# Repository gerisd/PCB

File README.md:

# PCB
PCB Hardware Design

# Overview

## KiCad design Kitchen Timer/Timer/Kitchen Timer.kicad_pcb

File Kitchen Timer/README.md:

# Kitchen Timer

## Results
### Schematic

### PCB 

### PCB 3D View

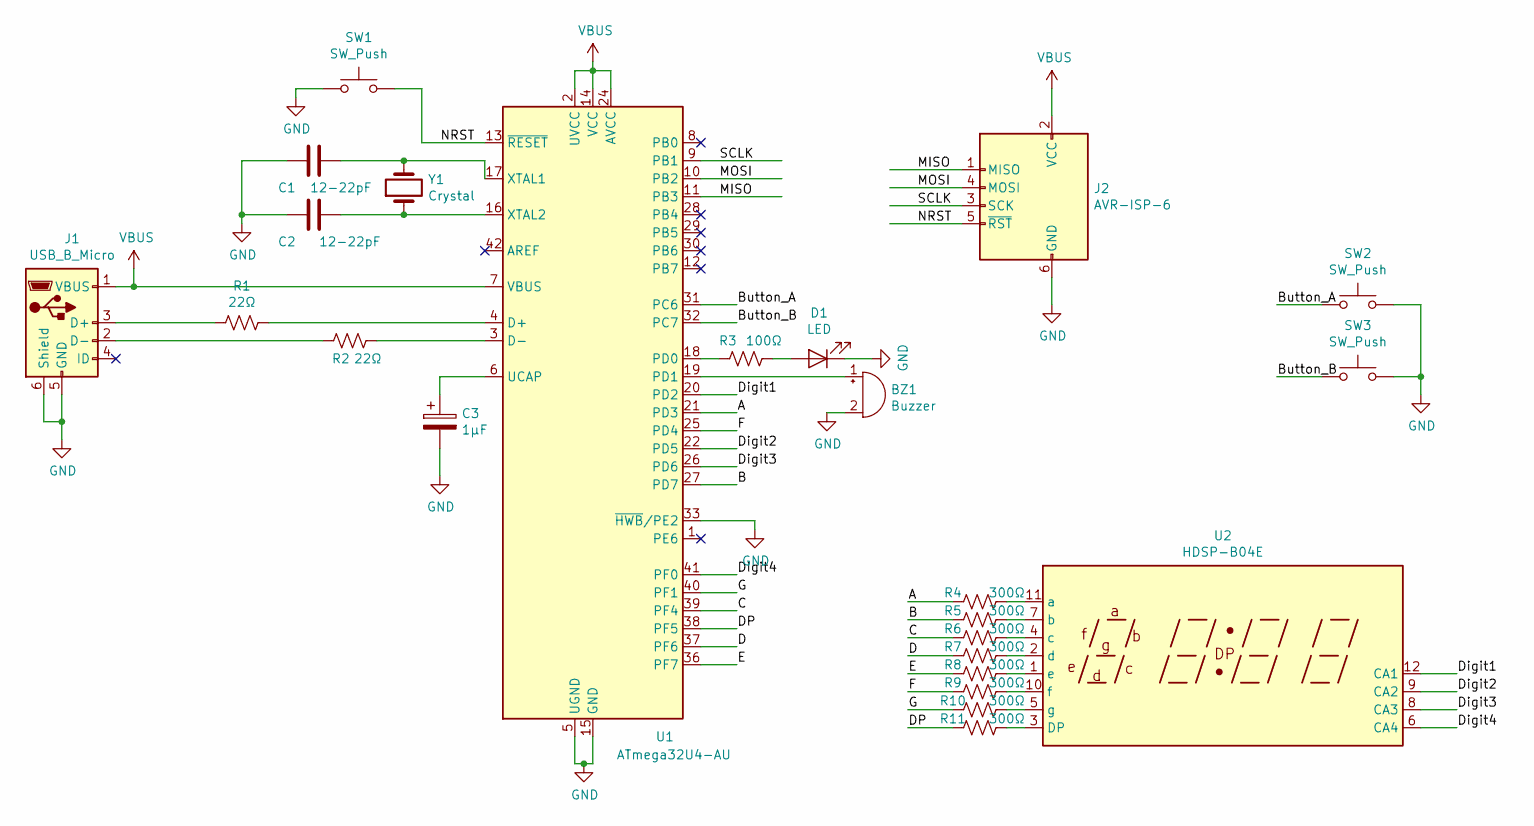
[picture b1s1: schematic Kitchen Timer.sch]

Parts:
BZ1: Buzzer; Buzzer_12x9.5RM7.6
C1, C2: 12-22pF; C_1206_3216Metric_Pad1.42x1.75mm_HandSolder
C3: 1μF; C_1206_3216Metric_Pad1.42x1.75mm_HandSolder
D1: LED; LED_0805_2012Metric_Pad1.15x1.40mm_HandSolder
J1: USB_B_Micro; USB_Micro-B_GCT_USB3076-30-A
J2: AVR-ISP-6; IDC-Header_2x03_P2.54mm_Vertical
R1, R2: 22Ω; R_1206_3216Metric_Pad1.42x1.75mm_HandSolder
R3: 100Ω; R_1206_3216Metric_Pad1.42x1.75mm_HandSolder
R4, R5, R6, R7, R8, R9, R10, R11: 300Ω; R_1206_3216Metric_Pad1.42x1.75mm_HandSolder
SW1, SW2, SW3: SW_Push; SW_PUSH_6mm
U1: ATmega32U4-AU; TQFP-44_10x10mm_P0.8mm
U2: HDSP-B04E; CA56-12CGKWA
Y1: Crystal; Crystal_SMD_HC49-SD_HandSoldering

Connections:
/A: R4.2, U1.21 (PD3)
/B: R5.2, U1.27 (PD7)
/Button_A: SW2.1, U1.31 (PC6)
/Button_B: SW3.1, U1.32 (PC7)
/C: R6.2, U1.39 (PF4)
/D: R7.2, U1.37 (PF6)
/DP: R11.2, U1.38 (PF5)
/Digit1: U1.20 (PD2), U2.12 (CA1)
/Digit2: U1.22 (PD5), U2.9 (CA2)
/Digit3: U1.26 (PD6), U2.8 (CA3)
/Digit4: U1.41 (PF0), U2.6 (CA4)
/E: R8.2, U1.36 (PF7)
/F: R9.2, U1.25 (PD4)
/G: R10.2, U1.40 (PF1)
/MISO: J2.1 (MISO), U1.11 (PB3)
/MOSI: J2.4 (MOSI), U1.10 (PB2)
/NRST: J2.5 (~RST), SW1.2, U1.13 (~RESET)
/SCLK: J2.3 (SCK), U1.9 (PB1)
GND: BZ1.2 (+), C1.2, C2.2, C3.2, D1.1 (K), J1.5 (GND), J1.6 (Shield), J2.6 (GND), SW1.1, SW2.2, SW3.2, U1.5 (UGND), U1.15 (GND), U1.23 (GND), U1.33 (~HWB~/PE2), U1.35 (GND), U1.43 (GND)
unnamed: BZ1.1 (-), U1.19 (PD1)
unnamed: C1.1, U1.17 (XTAL1), Y1.2
unnamed: C2.1, U1.16 (XTAL2), Y1.1
unnamed: C3.1, U1.6 (UCAP)
unnamed: D1.2 (A), R3.1
unnamed: J1.2 (D-), R2.2
unnamed: J1.3 (D+), R1.2
unnamed: R1.1, U1.4 (D+)
unnamed: R2.1, U1.3 (D-)
unnamed: R3.2, U1.18 (PD0)
unnamed: R4.1, U2.11 (a)
unnamed: R5.1, U2.7 (b)
unnamed: R6.1, U2.4 (c)
unnamed: R7.1, U2.2 (d)
unnamed: R8.1, U2.1 (e)
unnamed: R9.1, U2.10 (f)
unnamed: R10.1, U2.5 (g)
unnamed: R11.1, U2.3 (DP)
VBUS: J1.1 (VBUS), J2.2 (VCC), U1.2 (UVCC), U1.7 (VBUS), U1.14 (VCC), U1.24 (AVCC), U1.34 (VCC), U1.44 (AVCC)

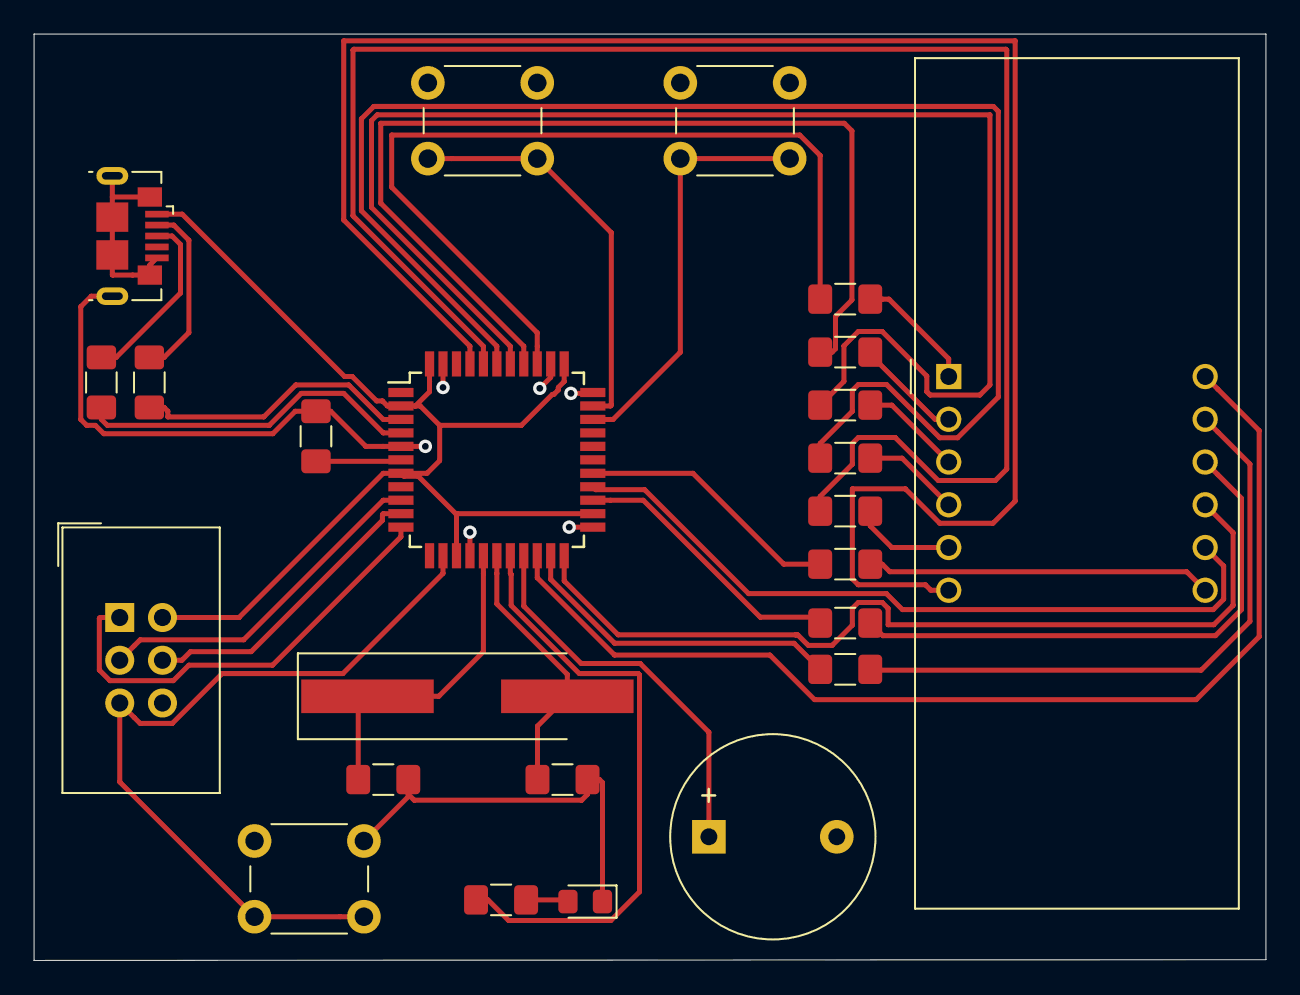
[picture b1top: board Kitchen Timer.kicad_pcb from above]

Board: 2 copper layers, 73.2 x 55.0 mm, 24 parts (0 on the bottom side), 38 nets.

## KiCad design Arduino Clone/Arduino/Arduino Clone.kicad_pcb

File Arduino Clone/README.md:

# Battery Powered Arduino Clone with External EEPROM

## Results
### Schematic

### PCB 

### PCB 3D View

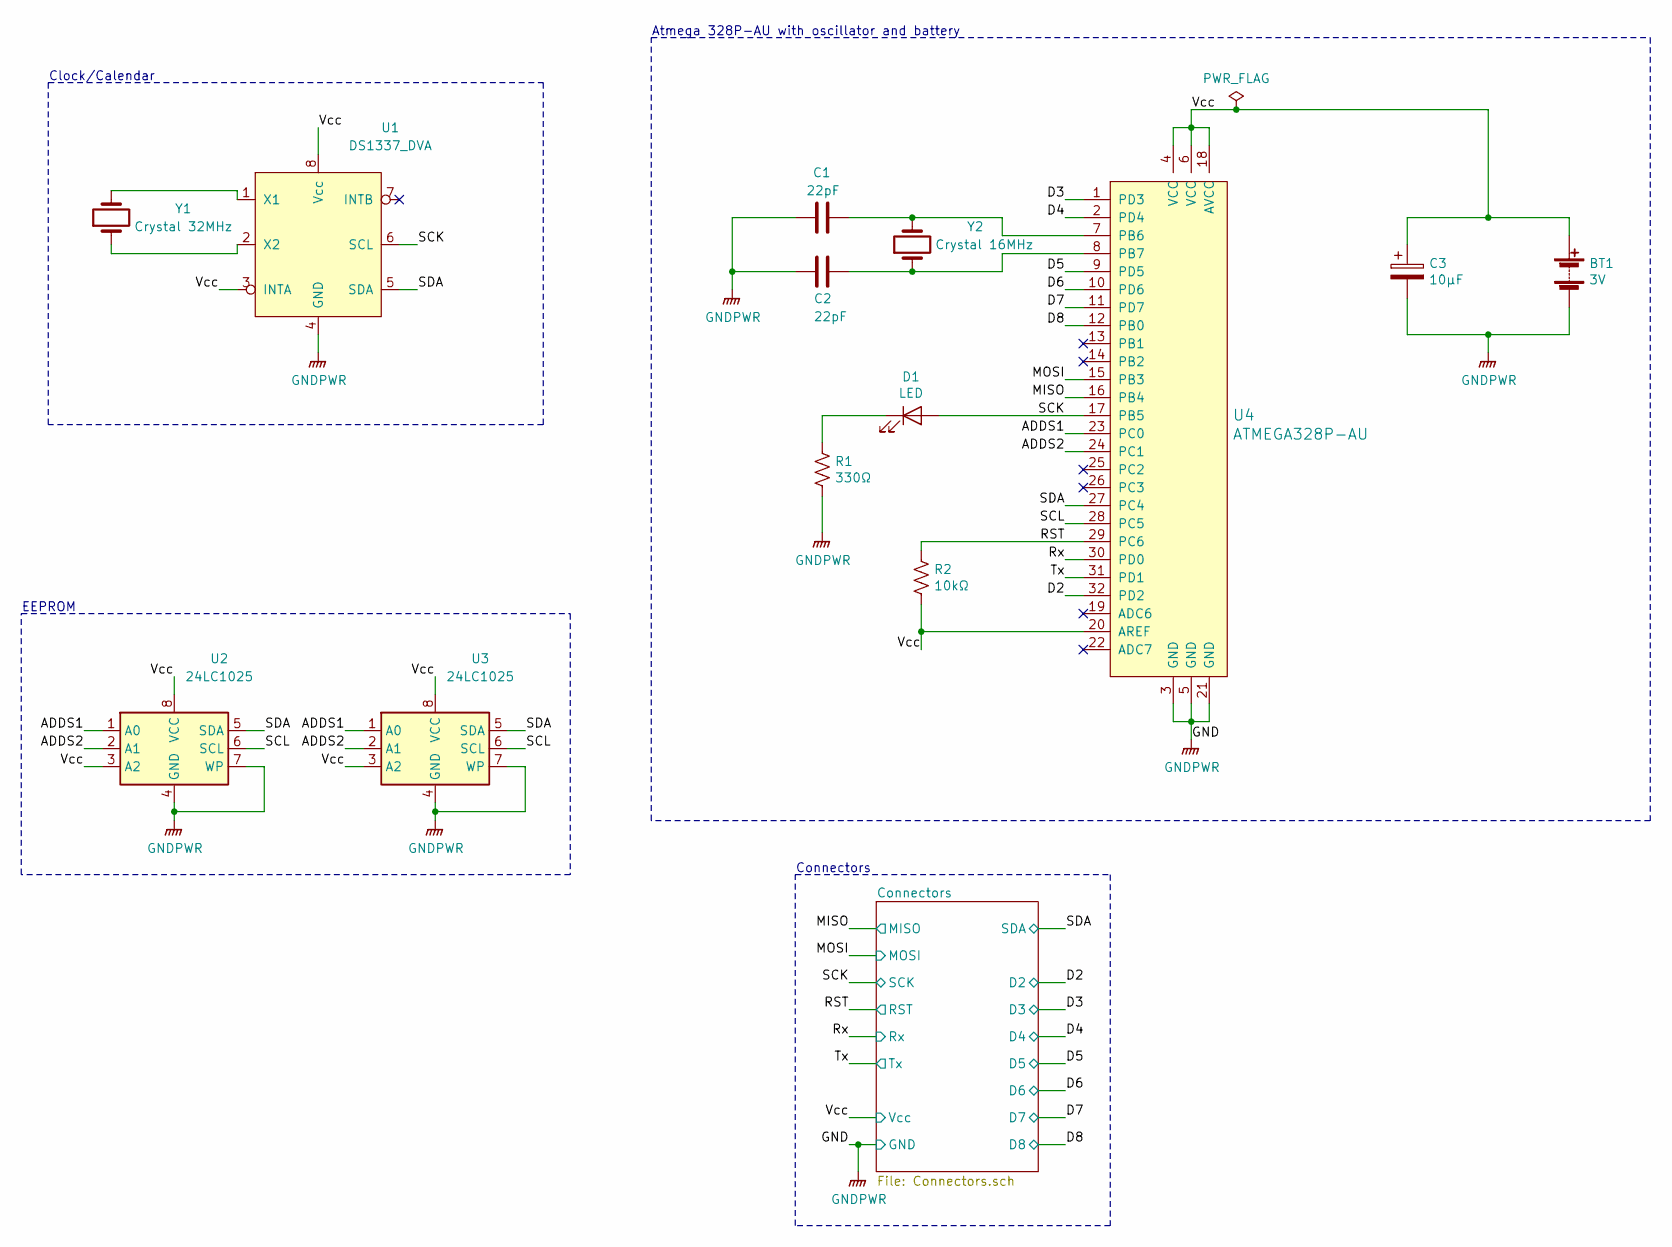
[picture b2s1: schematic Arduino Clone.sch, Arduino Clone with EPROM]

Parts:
BT1: 3V; PinHeader_1x02_P2.54mm_Vertical
C1, C2: 22pF; C_0805_2012Metric_Pad1.15x1.40mm_HandSolder
C3: 10μF; C_0805_2012Metric_Pad1.15x1.40mm_HandSolder
D1: LED; LED_0805_2012Metric_Pad1.15x1.40mm_HandSolder
R1: 330Ω; R_0805_2012Metric_Pad1.15x1.40mm_HandSolder
R2: 10kΩ; R_0805_2012Metric_Pad1.15x1.40mm_HandSolder
U1: DS1337_DVA; SO-8_5.3x6.2mm_P1.27mm
U2, U3: 24LC1025; SOIJ-8_5.3x5.3mm_P1.27mm
U4: ATMEGA328P-AU; TQFP-32_7x7mm; MPN ATMEGA328P-AU; Digi-Key_PN ATMEGA328P-AU-ND
Y1: Crystal 32MHz; Crystal_SMD_MicroCrystal_CC7V-T1A-2Pin_3.2x1.5mm
Y2: Crystal 16MHz; Crystal_SMD_5032-2Pin_5.0x3.2mm_HandSoldering

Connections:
/ADDS1: U2.1 (A0), U3.1 (A0), U4.23 (PC0)
/ADDS2: U2.2 (A1), U3.2 (A1), U4.24 (PC1)
/D2: U4.32 (PD2); also elsewhere on the board
/D3: U4.1 (PD3); also elsewhere on the board
/D4: U4.2 (PD4); also elsewhere on the board
/D5: U4.9 (PD5); also elsewhere on the board
/D6: U4.10 (PD6); also elsewhere on the board
/D7: U4.11 (PD7); also elsewhere on the board
/D8: U4.12 (PB0); also elsewhere on the board
/MISO: U4.16 (PB4); also elsewhere on the board
/MOSI: U4.15 (PB3); also elsewhere on the board
/RST: R2.1, U4.29 (PC6); also elsewhere on the board
/Rx: U4.30 (PD0); also elsewhere on the board
/SCK: D1.2 (A), U1.6 (SCL), U4.17 (PB5); also elsewhere on the board
/SCL: U2.6 (SCL), U3.6 (SCL), U4.28 (PC5)
/SDA: U1.5 (SDA), U2.5 (SDA), U3.5 (SDA), U4.27 (PC4); also elsewhere on the board
/Tx: U4.31 (PD1); also elsewhere on the board
/Vcc: BT1.1 (+), C3.1, R2.2, U1.3 (INTA), U1.8 (Vcc), U2.3 (A2), U2.8 (VCC), U3.3 (A2), U3.8 (VCC), U4.4 (VCC), U4.6 (VCC), U4.18 (AVCC), U4.20 (AREF); also elsewhere on the board
GNDPWR: BT1.2 (-), C1.1, C2.2, C3.2, R1.2, U1.4 (GND), U2.4 (GND), U2.7 (WP), U3.4 (GND), U3.7 (WP), U4.3 (GND), U4.5 (GND), U4.21 (GND); also elsewhere on the board
unnamed: C1.2, U4.7 (PB6), Y2.2
unnamed: C2.1, U4.8 (PB7), Y2.1
unnamed: D1.1 (K), R1.1
unnamed: U1.1 (X1), Y1.2
unnamed: U1.2 (X2), Y1.1

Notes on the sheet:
Clock/Calendar
EEPROM
Atmega 328P-AU with oscillator and battery
Connectors

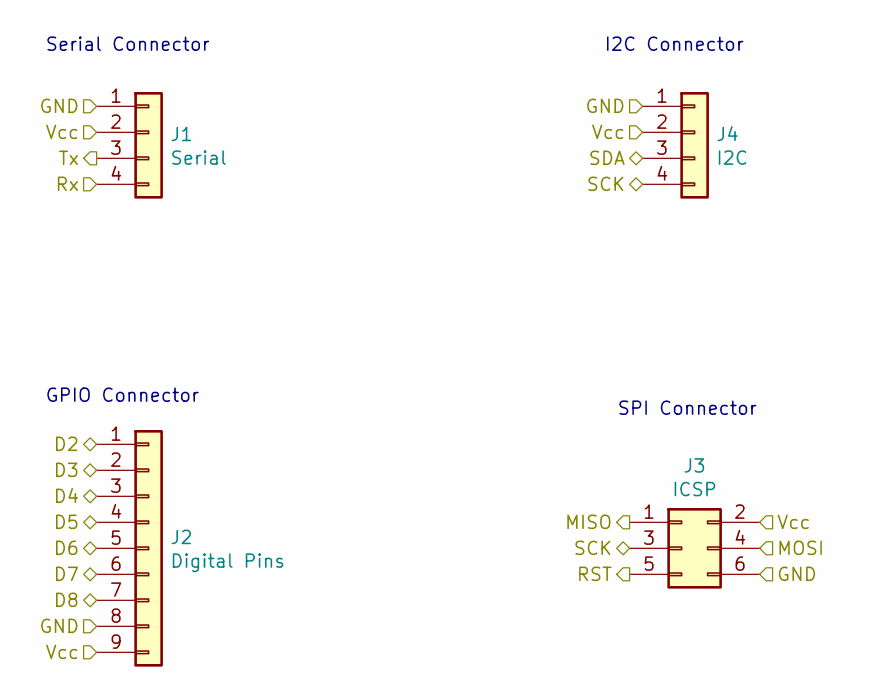
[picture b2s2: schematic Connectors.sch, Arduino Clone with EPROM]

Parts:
J1: Serial; PinSocket_1x04_P2.54mm_Vertical
J2: Digital Pins; PinSocket_1x09_P2.54mm_Vertical
J3: ICSP; PinSocket_2x03_P2.54mm_Vertical
J4: I2C; PinSocket_1x04_P2.54mm_Vertical

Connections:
/D2: J2.1; also elsewhere on the board
/D3: J2.2; also elsewhere on the board
/D4: J2.3; also elsewhere on the board
/D5: J2.4; also elsewhere on the board
/D6: J2.5; also elsewhere on the board
/D7: J2.6; also elsewhere on the board
/D8: J2.7; also elsewhere on the board
/MISO: J3.1; also elsewhere on the board
/MOSI: J3.4; also elsewhere on the board
/RST: J3.5; also elsewhere on the board
/Rx: J1.4; also elsewhere on the board
/SCK: J3.3, J4.4; also elsewhere on the board
/SDA: J4.3; also elsewhere on the board
/Tx: J1.3; also elsewhere on the board
/Vcc: J1.2, J2.9, J3.2, J4.2; also elsewhere on the board
GNDPWR: J1.1, J2.8, J3.6, J4.1; also elsewhere on the board

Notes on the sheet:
Serial Connector
I2C Connector
GPIO Connector
SPI Connector

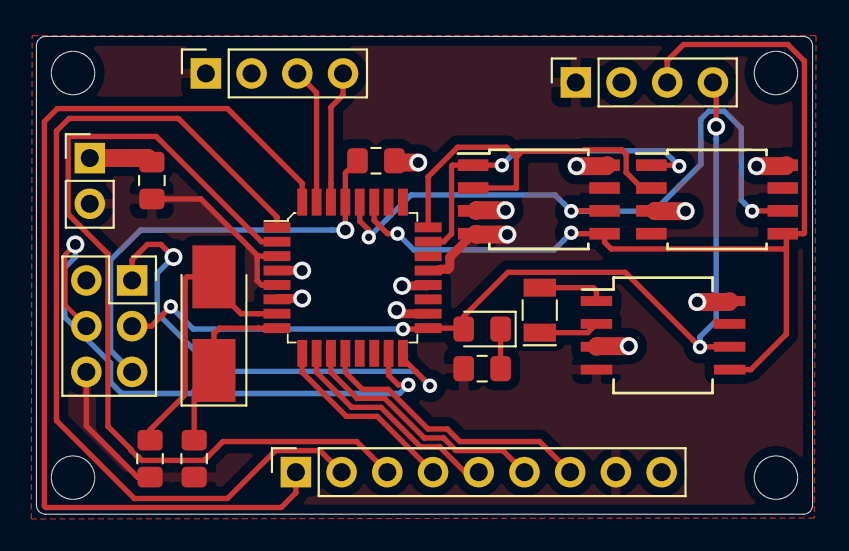
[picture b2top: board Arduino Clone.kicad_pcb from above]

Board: 4 copper layers, 43.1 x 26.5 mm, 17 parts (0 on the bottom side), 24 nets.

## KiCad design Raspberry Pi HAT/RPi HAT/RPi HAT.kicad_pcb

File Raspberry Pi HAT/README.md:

# Raspberry Pi HAT

## Results
### Schematic

### PCB 

### PCB 3D View

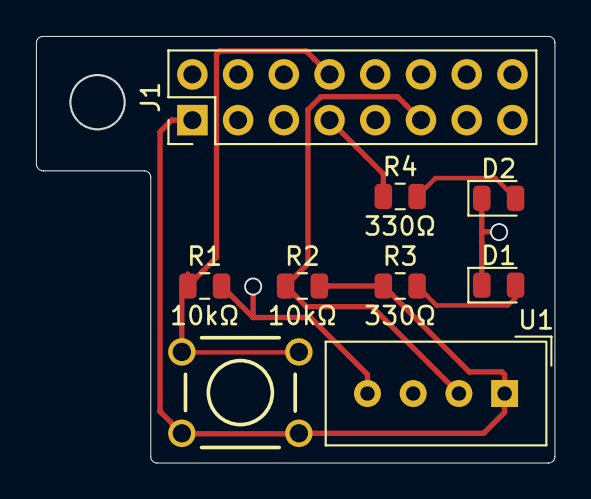
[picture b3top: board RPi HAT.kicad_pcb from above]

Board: 2 copper layers, 28.8 x 23.7 mm, 9 parts (0 on the bottom side), 7 nets.

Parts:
D1, D2: LED; LED_0805_2012Metric
J1: Raspberry_Pi_2_3; PinHeader_2x08_P2.54mm_Vertical
R1, R2: 10kΩ; R_0805_2012Metric
R3, R4: 330Ω; R_0805_2012Metric
SW1: SW_DPST; SW_PUSHBUTTON_PTH
U1: DHT22; Aosong_DHT11_5.5x12.0_P2.54mm

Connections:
/3.3V: J1.1, R2.2, R3.1, SW1.1, U1.1
GND: D1.1, D2.1, J1.6, J1.9, R1.2, U1.4
unnamed: D1.2, R3.2
unnamed: D2.2, R4.2
unnamed: J1.7, R4.1
unnamed: J1.8, R1.1, SW1.2
unnamed: J1.11, R2.1, U1.2

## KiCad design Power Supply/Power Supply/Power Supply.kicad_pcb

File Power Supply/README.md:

# Power Supply

## Results
### Schematic

### PCB 

### PCB 3D View

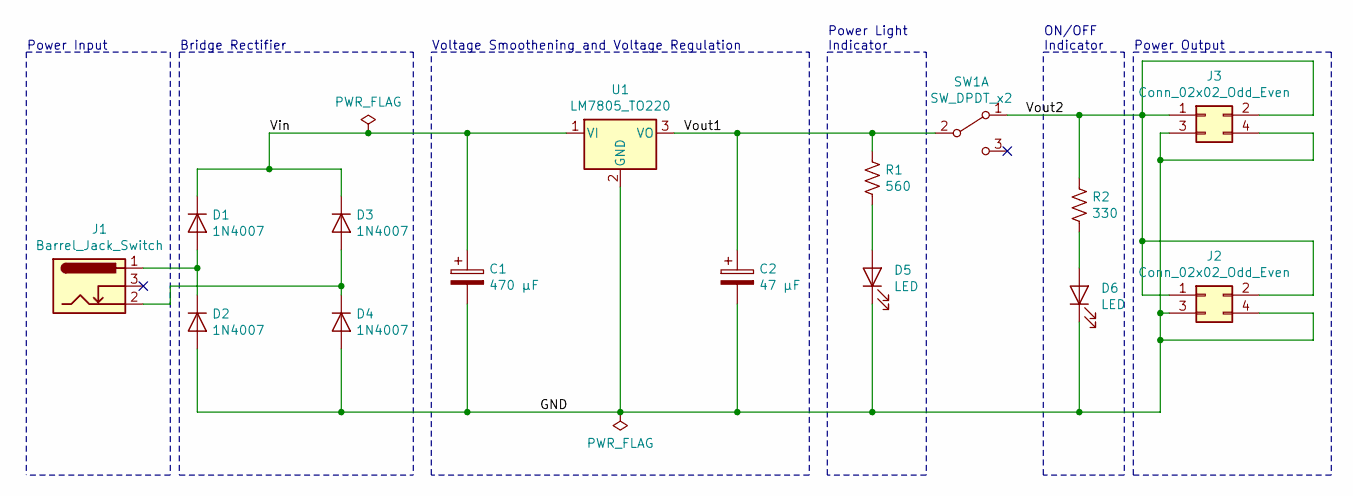
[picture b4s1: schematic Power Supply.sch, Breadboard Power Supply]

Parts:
C1: 470 µF; CP_Radial_D10.0mm_P5.00mm
C2: 47 µF; CP_Radial_D6.3mm_P2.50mm
D1, D2, D3, D4: 1N4007; D_DO-41_SOD81_P10.16mm_Horizontal
D5, D6: LED; LED_D5.0mm
J1: Barrel_Jack_Switch; BarrelJack_CUI_PJ-102AH_Horizontal
J2, J3: Conn_02x02_Odd_Even; PinHeader_2x02_P2.54mm_Vertical
R1: 560; R_Axial_DIN0207_L6.3mm_D2.5mm_P7.62mm_Horizontal
R2: 330; R_Axial_DIN0207_L6.3mm_D2.5mm_P7.62mm_Horizontal
SW1: SW_DPDT_x2; Switch_Slide_11.6x4mm_EG1218
U1: LM7805_TO220; TO-220-3_Vertical

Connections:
/GND: C1.2, C2.2, D2.2 (A), D4.2 (A), D5.1 (K), D6.1 (K), J2.3, J2.4, J3.3, J3.4, U1.2 (GND)
/Vin: C1.1, D1.1 (K), D3.1 (K), U1.1 (VI)
/Vout1: C2.1, R1.1, SW1.2 (B), U1.3 (VO)
/Vout2: J2.1, J2.2, J3.1, J3.2, R2.1, SW1.1 (A)
unnamed: D1.2 (A), D2.1 (K), J1.1
unnamed: D3.2 (A), D4.1 (K), J1.2
unnamed: D5.2 (A), R1.2
unnamed: D6.2 (A), R2.2

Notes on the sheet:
Power Input
Bridge Rectifier
Voltage Smoothening and Voltage Regulation
Power Light Indicator
ON/OFF Indicator
Power Output

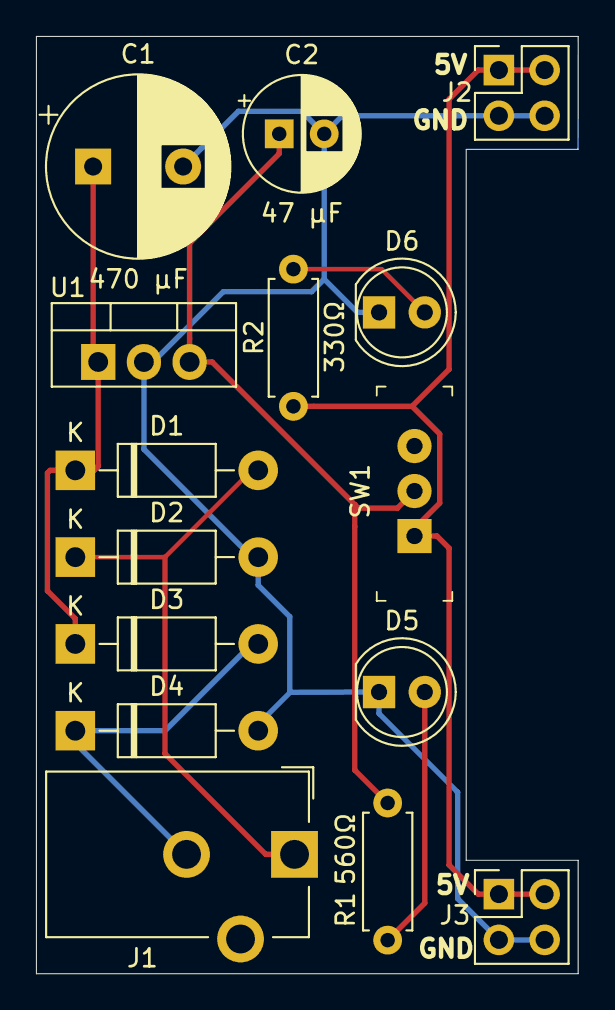
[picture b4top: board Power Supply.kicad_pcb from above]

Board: 2 copper layers, 30.1 x 52.1 mm, 15 parts (0 on the bottom side), 8 nets.

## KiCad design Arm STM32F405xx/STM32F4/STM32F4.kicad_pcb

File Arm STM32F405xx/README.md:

# ARM STM32F405xx 

## Results 
### Schematic

### PCB 

### PCB 3D View

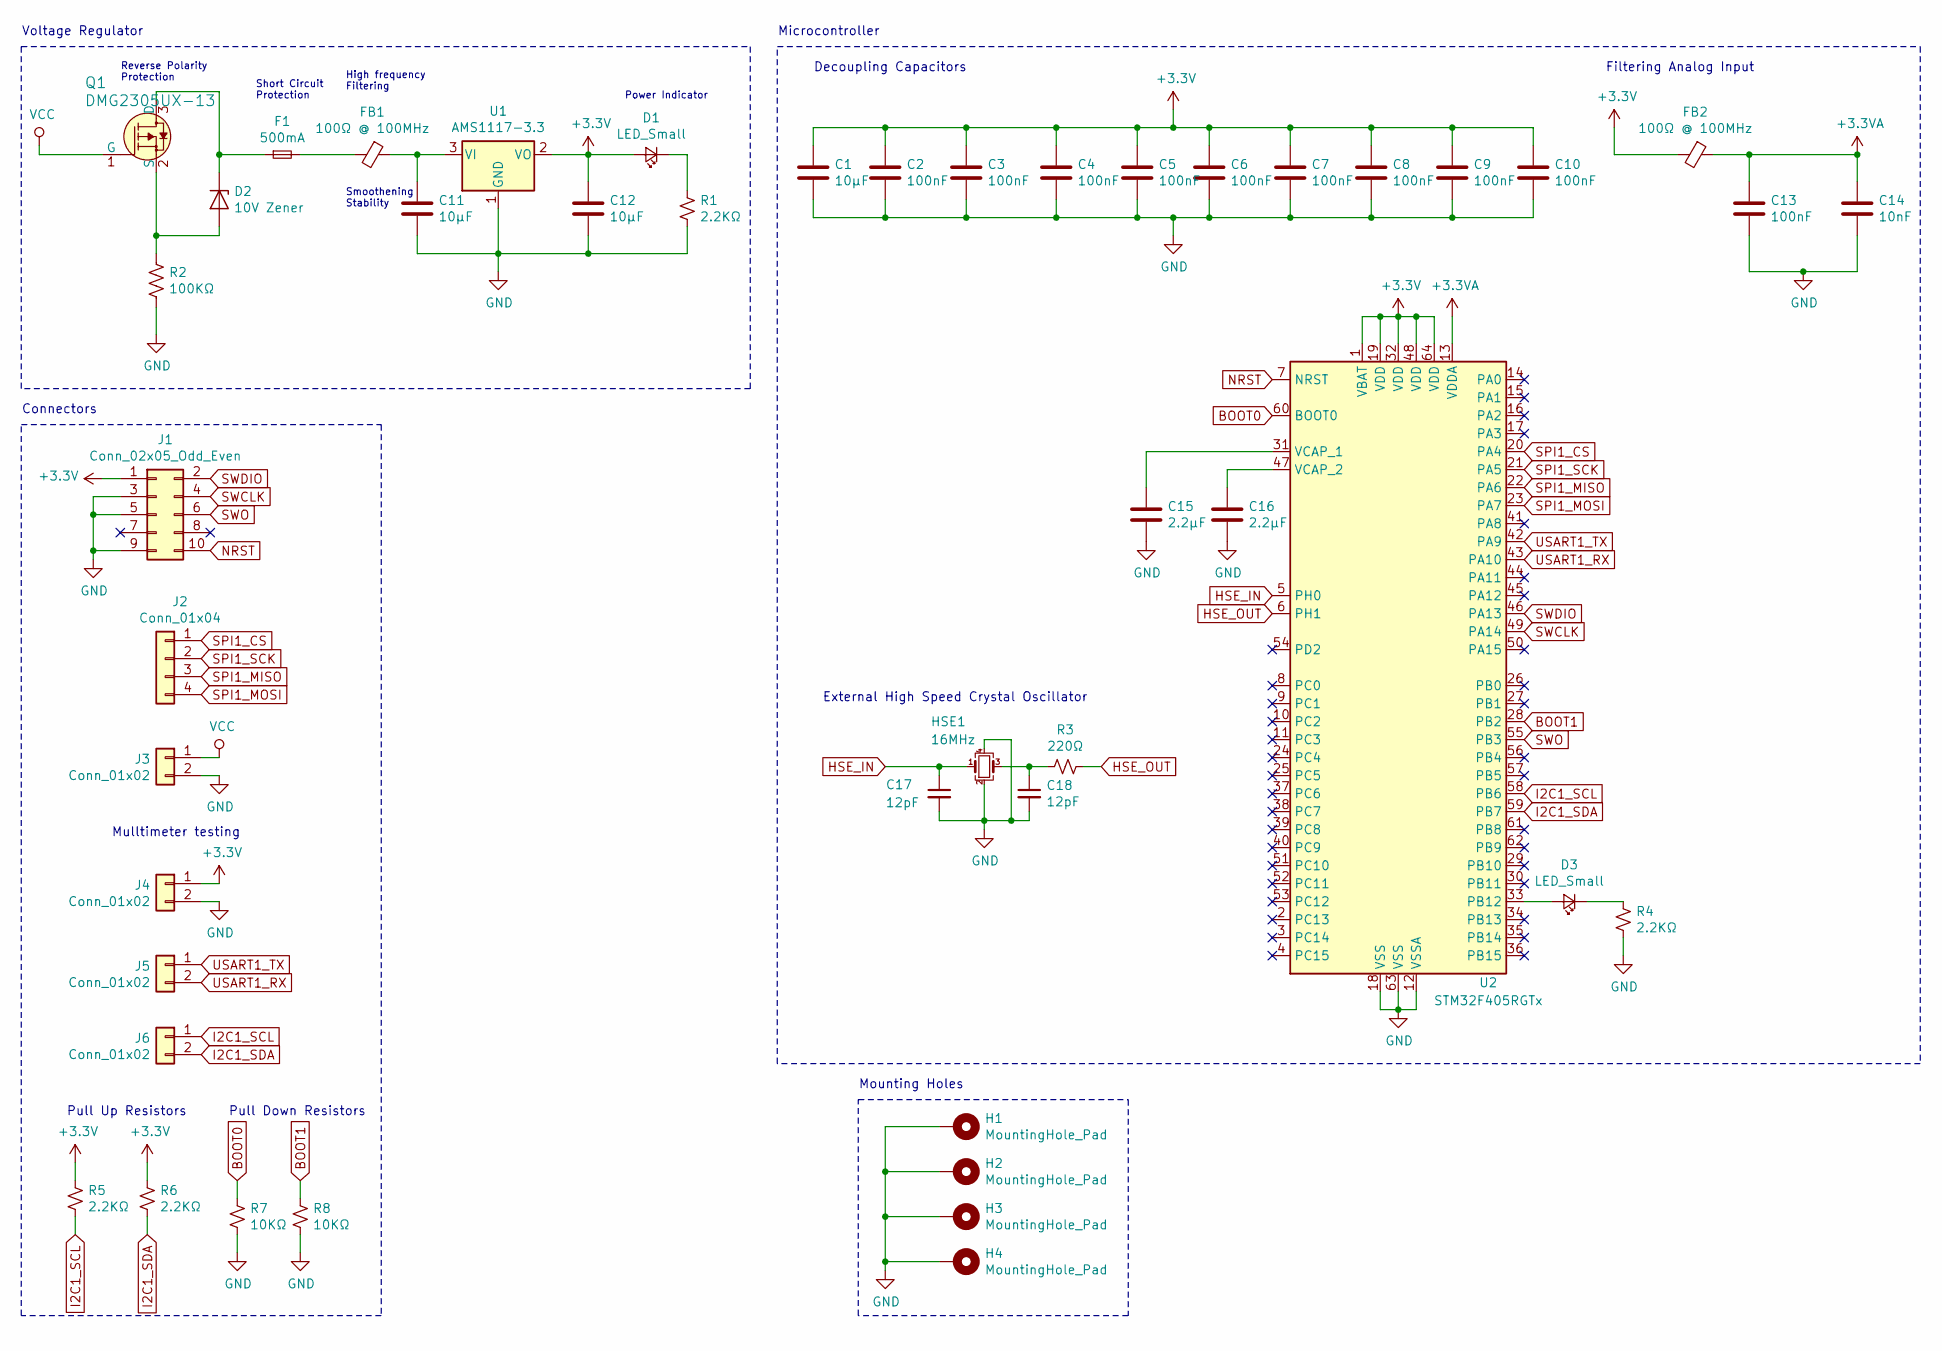
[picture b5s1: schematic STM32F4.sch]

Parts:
C1: 10μF; C_0603_1608Metric
C2, C3, C4, C5, C6, C7, C8, C9, C10, C13: 100nF; C_0402_1005Metric
C11, C12: 10μF; C_0805_2012Metric
C14: 10nF; C_0402_1005Metric
C15, C16: 2.2μF; C_0603_1608Metric
C17, C18: 12pF; C_0402_1005Metric
D1, D3: LED_Small; LED_0603_1608Metric
D2: 10V Zener; D_SOD-323
F1: 500mA; Fuse_0603_1608Metric
FB1, FB2: 100Ω @ 100MHz; L_0805_2012Metric
H1, H2, H3, H4: MountingHole_Pad; MountingHole_4.3mm_M4_Pad_Via
HSE1: 16MHz; Crystal_SMD_3225-4Pin_3.2x2.5mm
J1: Conn_02x05_Odd_Even; PinHeader_2x05_P2.54mm_Vertical_SMD
J2: Conn_01x04; PinHeader_1x04_P2.54mm_Vertical
J3, J4, J5, J6: Conn_01x02; PinHeader_1x02_P2.54mm_Vertical
Q1: DMG2305UX-13; SOT-23-3; MPN DMG2305UX-13; Digi-Key_PN DMG2305UX-13DICT-ND
R1, R4: 2.2KΩ; R_0603_1608Metric
R2: 100KΩ; R_0805_2012Metric
R3: 220Ω; R_0402_1005Metric
R5, R6: 2.2KΩ; R_0402_1005Metric
R7, R8: 10KΩ; R_0402_1005Metric
U1: AMS1117-3.3; SOT-223-3_TabPin2
U2: STM32F405RGTx; LQFP-64_10x10mm_P0.5mm

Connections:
+3.3VA: C13.1, C14.1, FB2.1, U2.13 (VDDA)
+3V3: C1.1, C2.1, C3.1, C4.1, C5.1, C6.1, C7.1, C8.1, C9.1, C10.1, C12.1, D1.2 (A), FB2.2, J1.1, J4.1, R5.2, R6.2, U1.2 (VO), U2.1 (VBAT), U2.19 (VDD), U2.32 (VDD), U2.48 (VDD), U2.64 (VDD)
BOOT0: R7.2, U2.60 (BOOT0)
BOOT1: R8.2, U2.28 (PB2)
GND: C1.2, C2.2, C3.2, C4.2, C5.2, C6.2, C7.2, C8.2, C9.2, C10.2, C11.2, C12.2, C13.2, C14.2, C15.2, C16.2, C17.2, C18.2, H1.1, H2.1, H3.1, H4.1, HSE1.2, HSE1.4, J1.3, J1.5, J1.9, J3.2, J4.2, R1.1, R2.2, R4.1, R7.1, R8.1, U1.1 (GND), U2.12 (VSSA), U2.18 (VSS), U2.63 (VSS)
HSE_IN: C17.1, HSE1.1, U2.5 (PH0)
HSE_OUT: R3.1, U2.6 (PH1)
I2C1_SCL: J6.1, R5.1, U2.58 (PB6)
I2C1_SDA: J6.2, R6.1, U2.59 (PB7)
NRST: J1.10, U2.7 (NRST)
unnamed: C11.1, FB1.1, U1.3 (VI)
unnamed: C15.1, U2.31 (VCAP_1)
unnamed: C16.1, U2.47 (VCAP_2)
unnamed: C18.1, HSE1.3, R3.2
unnamed: D1.1 (K), R1.2
unnamed: D2.1 (K), F1.1, Q1.3 (D)
unnamed: D2.2 (A), Q1.2 (S), R2.1
unnamed: D3.1 (K), R4.2
unnamed: D3.2 (A), U2.33 (PB12)
unnamed: F1.2, FB1.2
SPI1_CS: J2.1, U2.20 (PA4)
SPI1_MISO: J2.3, U2.22 (PA6)
SPI1_MOSI: J2.4, U2.23 (PA7)
SPI1_SCK: J2.2, U2.21 (PA5)
SWCLK: J1.4, U2.49 (PA14)
SWDIO: J1.2, U2.46 (PA13)
SWO: J1.6, U2.55 (PB3)
USART1_RX: J5.2, U2.43 (PA10)
USART1_TX: J5.1, U2.42 (PA9)
VCC: J3.1, Q1.1 (G)

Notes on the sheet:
Reverse Polarity Protection
Short Circuit Protection
High frequency Filtering
Smoothening Stability
Voltage Regulator
Decoupling Capacitors
Filtering Analog Input
Power Indicator
Pull Down Resistors
Pull Up Resistors
External High Speed Crystal Oscillator
Mulltimeter testing
Connectors
Microcontroller
Mounting Holes

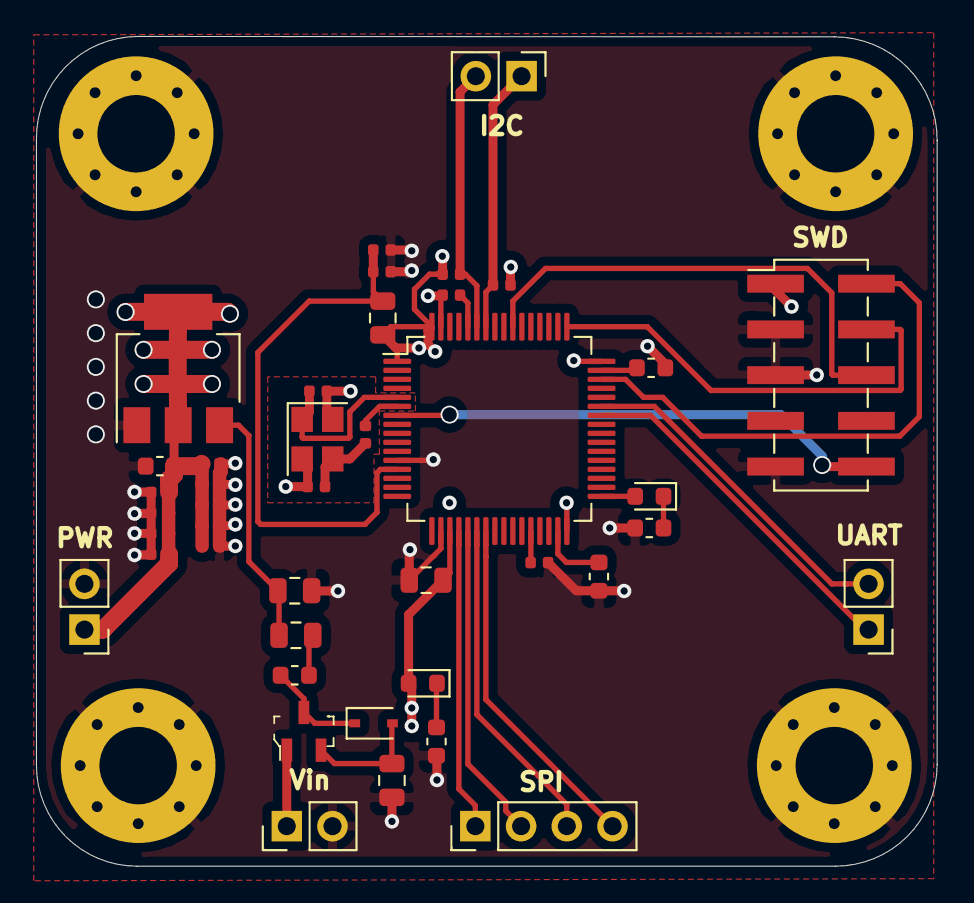
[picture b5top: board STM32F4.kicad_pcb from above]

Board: 4 copper layers, 50.0 x 46.1 mm, 46 parts (0 on the bottom side), 30 nets.
